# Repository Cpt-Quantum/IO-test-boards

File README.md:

This repository contains boards for the purpose of easy testing of GPIO when
bringing up a new board. The LED board design provides buffered inputs for
switching any of 8 LEDs from 8 inputs. The switch board provides 8 outputs from
a DIP switch.

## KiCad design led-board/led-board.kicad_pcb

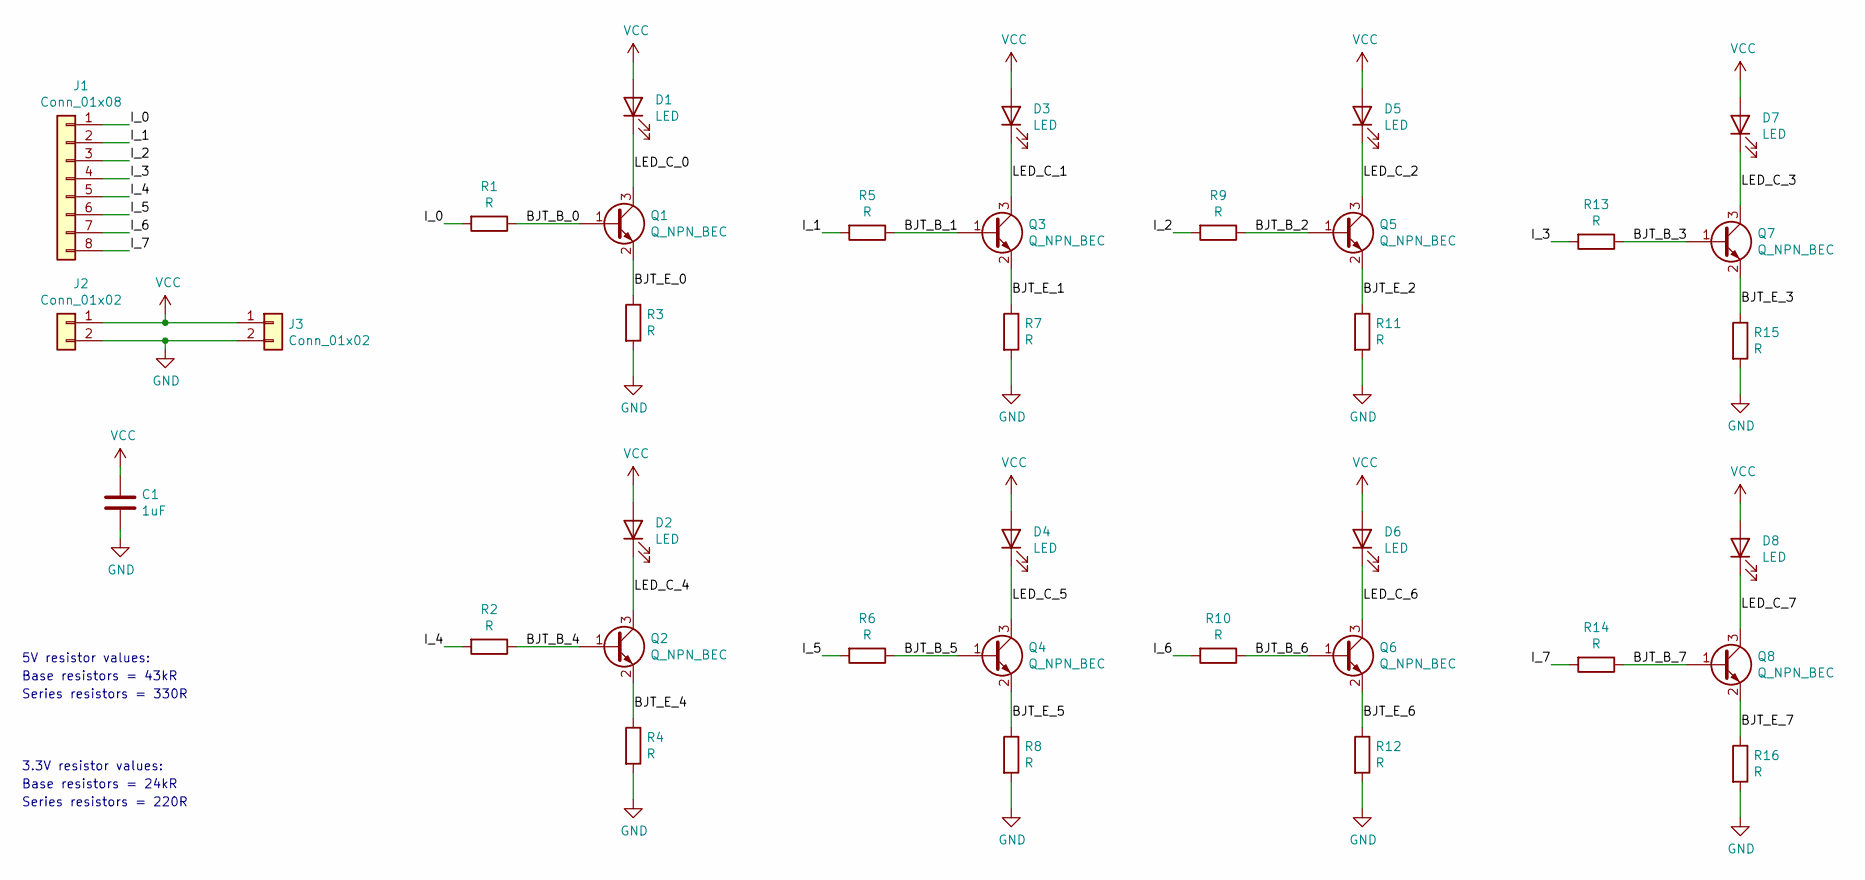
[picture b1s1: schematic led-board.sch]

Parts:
C1: 1uF; C_0603_1608Metric
D1, D2, D3, D4, D5, D6, D7, D8: LED; LED_0603_1608Metric
J1: Conn_01x08; PinHeader_1x08_P2.54mm_Vertical
J2, J3: Conn_01x02; PinHeader_1x02_P2.54mm_Vertical
Q1, Q2, Q3, Q4, Q5, Q6, Q7, Q8: Q_NPN_BEC; SOT-23
R1, R2, R3, R4, R5, R6, R7, R8, R9, R10, R11, R12, R13, R14, R15, R16: R; R_0603_1608Metric

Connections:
/BJT_B_0: Q1.1 (B), R1.1
/BJT_B_1: Q3.1 (B), R5.1
/BJT_B_2: Q5.1 (B), R9.1
/BJT_B_3: Q7.1 (B), R13.1
/BJT_B_4: Q2.1 (B), R2.1
/BJT_B_5: Q4.1 (B), R6.1
/BJT_B_6: Q6.1 (B), R10.1
/BJT_B_7: Q8.1 (B), R14.1
/BJT_E_0: Q1.2 (E), R3.1
/BJT_E_1: Q3.2 (E), R7.1
/BJT_E_2: Q5.2 (E), R11.1
/BJT_E_3: Q7.2 (E), R15.1
/BJT_E_4: Q2.2 (E), R4.1
/BJT_E_5: Q4.2 (E), R8.1
/BJT_E_6: Q6.2 (E), R12.1
/BJT_E_7: Q8.2 (E), R16.1
/I_0: J1.1, R1.2
/I_1: J1.2, R5.2
/I_2: J1.3, R9.2
/I_3: J1.4, R13.2
/I_4: J1.5, R2.2
/I_5: J1.6, R6.2
/I_6: J1.7, R10.2
/I_7: J1.8, R14.2
/LED_C_0: D1.1 (K), Q1.3 (C)
/LED_C_1: D3.1 (K), Q3.3 (C)
/LED_C_2: D5.1 (K), Q5.3 (C)
/LED_C_3: D7.1 (K), Q7.3 (C)
/LED_C_4: D2.1 (K), Q2.3 (C)
/LED_C_5: D4.1 (K), Q4.3 (C)
/LED_C_6: D6.1 (K), Q6.3 (C)
/LED_C_7: D8.1 (K), Q8.3 (C)
GND: C1.2, J2.2, J3.2, R3.2, R4.2, R7.2, R8.2, R11.2, R12.2, R15.2, R16.2
VCC: C1.1, D1.2 (A), D2.2 (A), D3.2 (A), D4.2 (A), D5.2 (A), D6.2 (A), D7.2 (A), D8.2 (A), J2.1, J3.1

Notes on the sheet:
5V resistor values:
3.3V resistor values:
Base resistors = 43kR
Series resistors = 330R
Base resistors = 24kR
Series resistors = 220R

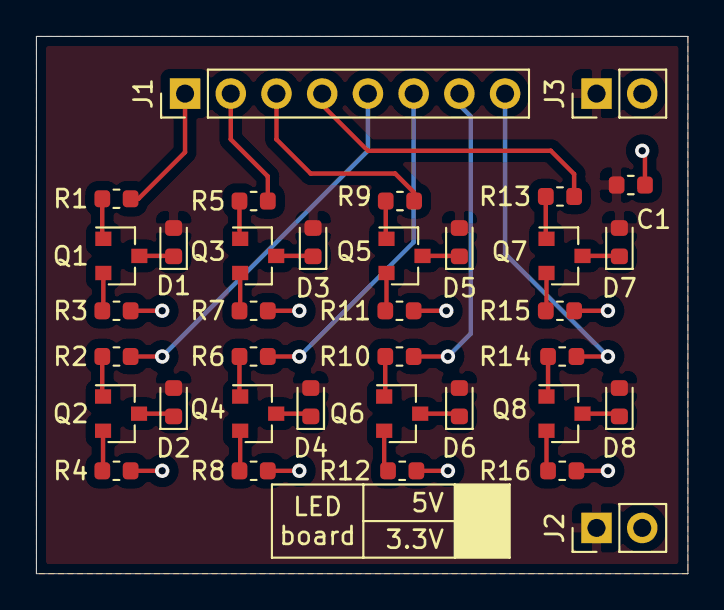
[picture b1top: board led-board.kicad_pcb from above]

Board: 2 copper layers, 36.2 x 29.8 mm, 36 parts (0 on the bottom side), 34 nets.

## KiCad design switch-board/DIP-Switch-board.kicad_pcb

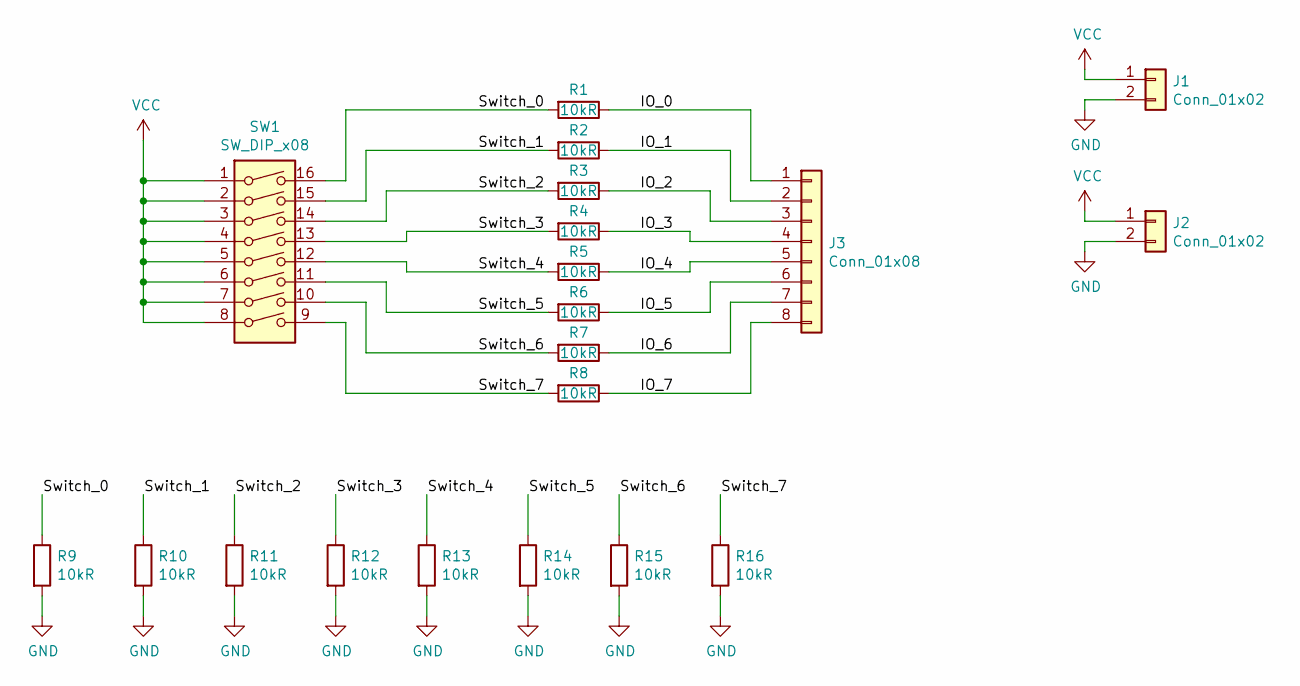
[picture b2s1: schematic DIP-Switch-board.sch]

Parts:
J1, J2: Conn_01x02; PinHeader_1x02_P2.54mm_Vertical
J3: Conn_01x08; PinHeader_1x08_P2.54mm_Vertical
R1, R2, R3, R4, R5, R6, R7, R8, R9, R10, R11, R12, R13, R14, R15, R16: 10kR; R_0603_1608Metric
SW1: SW_DIP_x08; SW_DIP_SPSTx08_Slide_9.78x22.5mm_W7.62mm_P2.54mm

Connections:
/IO_0: J3.1, R1.1
/IO_1: J3.2, R2.1
/IO_2: J3.3, R3.1
/IO_3: J3.4, R4.1
/IO_4: J3.5, R5.1
/IO_5: J3.6, R6.1
/IO_6: J3.7, R7.1
/IO_7: J3.8, R8.1
/Switch_0: R1.2, R9.1, SW1.16
/Switch_1: R2.2, R10.1, SW1.15
/Switch_2: R3.2, R11.1, SW1.14
/Switch_3: R4.2, R12.1, SW1.13
/Switch_4: R5.2, R13.1, SW1.12
/Switch_5: R6.2, R14.1, SW1.11
/Switch_6: R7.2, R15.1, SW1.10
/Switch_7: R8.2, R16.1, SW1.9
GND: J1.2, J2.2, R9.2, R10.2, R11.2, R12.2, R13.2, R14.2, R15.2, R16.2
VCC: J1.1, J2.1, SW1.1, SW1.2, SW1.3, SW1.4, SW1.5, SW1.6, SW1.7, SW1.8

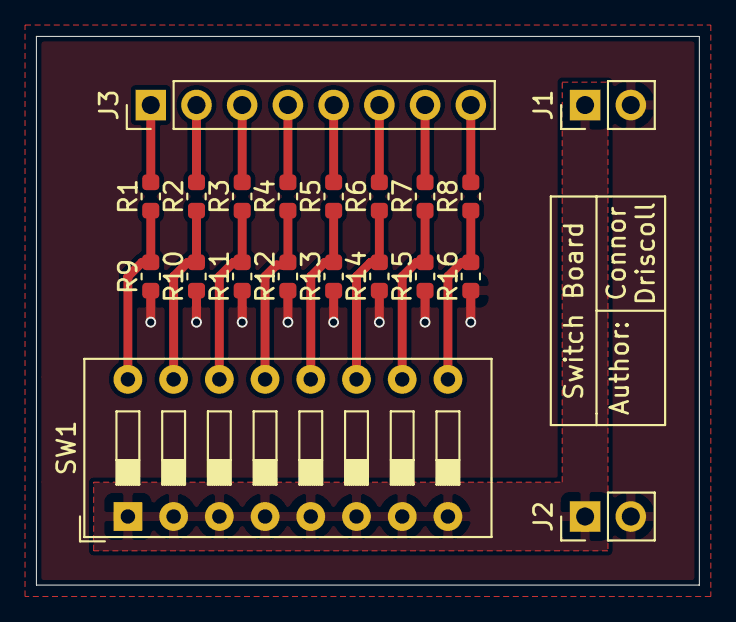
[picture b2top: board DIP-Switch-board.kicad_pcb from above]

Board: 2 copper layers, 36.8 x 30.5 mm, 20 parts (0 on the bottom side), 18 nets.

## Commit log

2020-09-09 Initial board/schematic files
2020-09-09 Cleaned directory structure for led-board
2020-09-09 Added README
2020-09-15 Added PDFs for each schematic
